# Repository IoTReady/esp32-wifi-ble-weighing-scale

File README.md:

# ESP32 Weighing Scale

This is a weighing scale designed to share data over Wi-Fi using esp32 WROOM32 module.
For the weighing scale we are using a load cell and measuring the output using a HX711 24-bit ADC designed for weigh scales and industrial control applications to interface directly with a bridge sensor.

The final design and gerber files are available [here](https://github.com/IoTReady/esp32-wifi-ble-weighing-scale/blob/master/design/Single_scale_v3_kicad/single_scale_v3_gerber.zip).

# Circuit Design
## Power Supply
We are using a 3.7V Li-Ion battery for powering this scale. The current rating can be changed depending on the use case. We also have a battery charging circuit on the board, so you don't have to remove the battery for charging it.

We use a TP4056 charging IC, as it is easily available and gives a reasonable 1000 mA output current, with 4.2V output voltage for charging the battery. For preventing the battery from over-charging and over-discharging, we use the DW01A protection IC. It is connected with a FS8205A switch IC, which will cut off the battery from the circuit if any fault is detected.

Finally, the 3.7V battery ouput is fed to two voltage regulators to get +5V and +3.3V output voltages as shown below:

## ADC Circuit
We are using HX711 24-bit ADC IC for converting the analog data from the Load cell. We selected HX711 as it is designed specifically for weighing scales, to interface with brige sensors directly. Load cells are basically bridge sensors.
As shown below the final output is in serial data output form. This is basically a UART output, and there are few digital pin controls.

## ESP32
The brains of our weighing scale, the esp32 wroom32 module is a BLE plus WiFi SoC which collects weight data from the ADC circuit and outputs the final processed data via a digital display and WiFi to the selected servers for maintaing inventories or doing any data analysis.

# PCB
This is what the final PCB looks like:

# Firmware

## Features
- 24 bit HX711 as ADC
- Any 4 wire load cell
- BLE communication
- Tare button
- Battery level monitor
- MAX7219 driven 7-segment display
- OTA (to be hosted from local network)
- Console setting of tare value and sensor calibration

### Weight Calculation
The HX711 is a great match for weighing use-cases. The 24 bit ADC is designed specifically for weight measurements and is directly interfaceable with load sensors and weigh bridges. There is no programming needed for the internal registers. All controls to the HX711 are through the pins. The HX711 component handles everything necessary for conversion to calibration. For more details, find the HX711 datasheet [here](https://cdn.sparkfun.com/datasheets/Sensors/ForceFlex/hx711_english.pdf)

### Factors for weight calculation/conversion
There are two major factors to consider in order to get an accurate calculation:
1. Tare Value (OFFSET): In weighment applications it is important to be able to reset the output value to zero if and when needed. In the firmware however, it is particularly important to understand the ADC output at zero. Any value higher or lower than this ADC value would result in positive or negative weight hereafter. Almost all weighing scales will provide a button for the users to return the current weight to zero. This is used to round off any extra weight that needs not be accounted, for example the container. In this application, the tare button has been assigned to GPIO19 on the ESP32.
  The auto-tare feature in the application tares the system at startup, such that the weighing scale always starts with a zero value. This eliminates human error. Make sure that there are no items placed on the platform and even the bottom of the scale is not in contact with any object at the time of starting up the machine until the display shows 0.
  
3. Calibration value (SCALE): The calibration value is the multiplication factor that needs to be multiplied to the ADC output value in order to get the real-time weight out of it in the units needed. This calibration value will be different for all individual load cells, hence it is important that all weighing machines go through a calibration procedure before they are shipped.

This application provides a simple method to set/calculate the above mentioned Tare and Calibration values:
- Start by placing the scale in a stable platform and environment. Please choose an area with minimum air currents and vibration levels.
- Connect your computer to the ESP32 controller's UART0 using an FTDI connector.
- You will need software to access the serial communication happening over the UART lines. For example, [PuTTY](https://www.putty.org/).
- While the program is flashed and running on the ESP32, press 'm' and hit Enter. You will be provided a menu using which you can access the tare and calibration features.
- For calibration, carry out the following steps:
  - You need to select a test value weight. This weight must be within the scale constraint and approximately 50% of the upper capacity. This should also be a known weight that you should possess.
  - Make sure that there are no items placed on the platform and even the bottom of the scale is not in contact with any object.
  - Make sure the console shows 0 weight. If not, press the tare button so the console shows 0.
  - Place the known selected weight on the platform of the weighing scale and view the weight on the console.
  - Follow the instructions to either change the calibration value or select the current selected calibration value if the weight shown on console is correct.
  - Repeat until the weight is correct.
  - Save

### BLE Characteristics:
| Service / Characteristics Name | UUID Handle                          | Properties | Description   |
|--------------------------------|--------------------------------------|------------|---------------|
| Device State Service           | 000000ff-0000-1000-8000-00805f9b34fb | Service    | -             |
| Weight Data                    | 0000ff00-0000-1000-8000-00805f9b34fb | Read       | Weight in kgs |

| Service / Characteristics Name  | UUID Handle                          | Properties  | Description                                                                                                       | Size            | Data Type        |
|---------------------------------|--------------------------------------|-------------|-------------------------------------------------------------------------------------------------------------------|-----------------|------------------|
| System Settings Service         | 000000ee-0000-1000-8000-00805f9b34fb | Service     | -                                                                                                                 | -               | -                |
| Device ID Characteristic        | 0000ee00-0000-1000-8000-00805f9b34fb | Read        | Read Device ID                                                                                                    | Length: 12      | String           |
| WiFi SSID  Characteristic       | 0000ee01-0000-1000-8000-00805f9b34fb | Read/Write  | WiFi SSID configured with the device                                                                              | Max Length: 32  | String           |
| WiFi Password Characteristic    | 0000ee02-0000-1000-8000-00805f9b34fb | Read/Write  | WiFi Password configured with the device                                                                          | Max Length: 32  | String           |
| OTA IP Characteristic           | 0000ee03-0000-1000-8000-00805f9b34fb | Read/Write  | Read/Write the IP of OTA host                                                                                     | Max Length: 100 | String           |
| OTA Port Characteristic         | 0000ee04-0000-1000-8000-00805f9b34fb | Read/Write  | Read/Write the Port of OTA host server                                                                            | Max Length: 100 | String           |
| OTA Filename Characteristic     | 0000ee05-0000-1000-8000-00805f9b34fb | Read/Write  | Read/Write the filename of OTA binary file                                                                        | Max Length: 100 | String           |
| Force OTA Characteristic        | 0000ee06-0000-1000-8000-00805f9b34fb | Write       | Initiate OTA procedure Value: ‘1’ [0x31]                                                                          | 1 byte          | Unsigned Integer |
| Tare Weight Characteristic      | 0000ee07-0000-1000-8000-00805f9b34fb | Write       | Cancel OTA procedure within 10 seconds of initiation Value: ‘1’ [0x31]                                            | 1 byte          | Unsigned Integer |
| Connect WiFi Characteristic     | 0000ee08-0000-1000-8000-00805f9b34fb | Write       | Connect to previously configured WiFi credentials. Value: ‘1’ [0x31]                                              | 1 byte          | Unsigned Integer |
| Software Version Characteristic | 0000ee09-0000-1000-8000-00805f9b34fb | Read        | Read the Software Version in the device                                                                           | -               | String           |
# Applications
This weighing scale is designed keeping in mind sharing of data over the internet. So, any application where we need to capture weight of things and maintain a record for any use, we can integrate this device in that system.

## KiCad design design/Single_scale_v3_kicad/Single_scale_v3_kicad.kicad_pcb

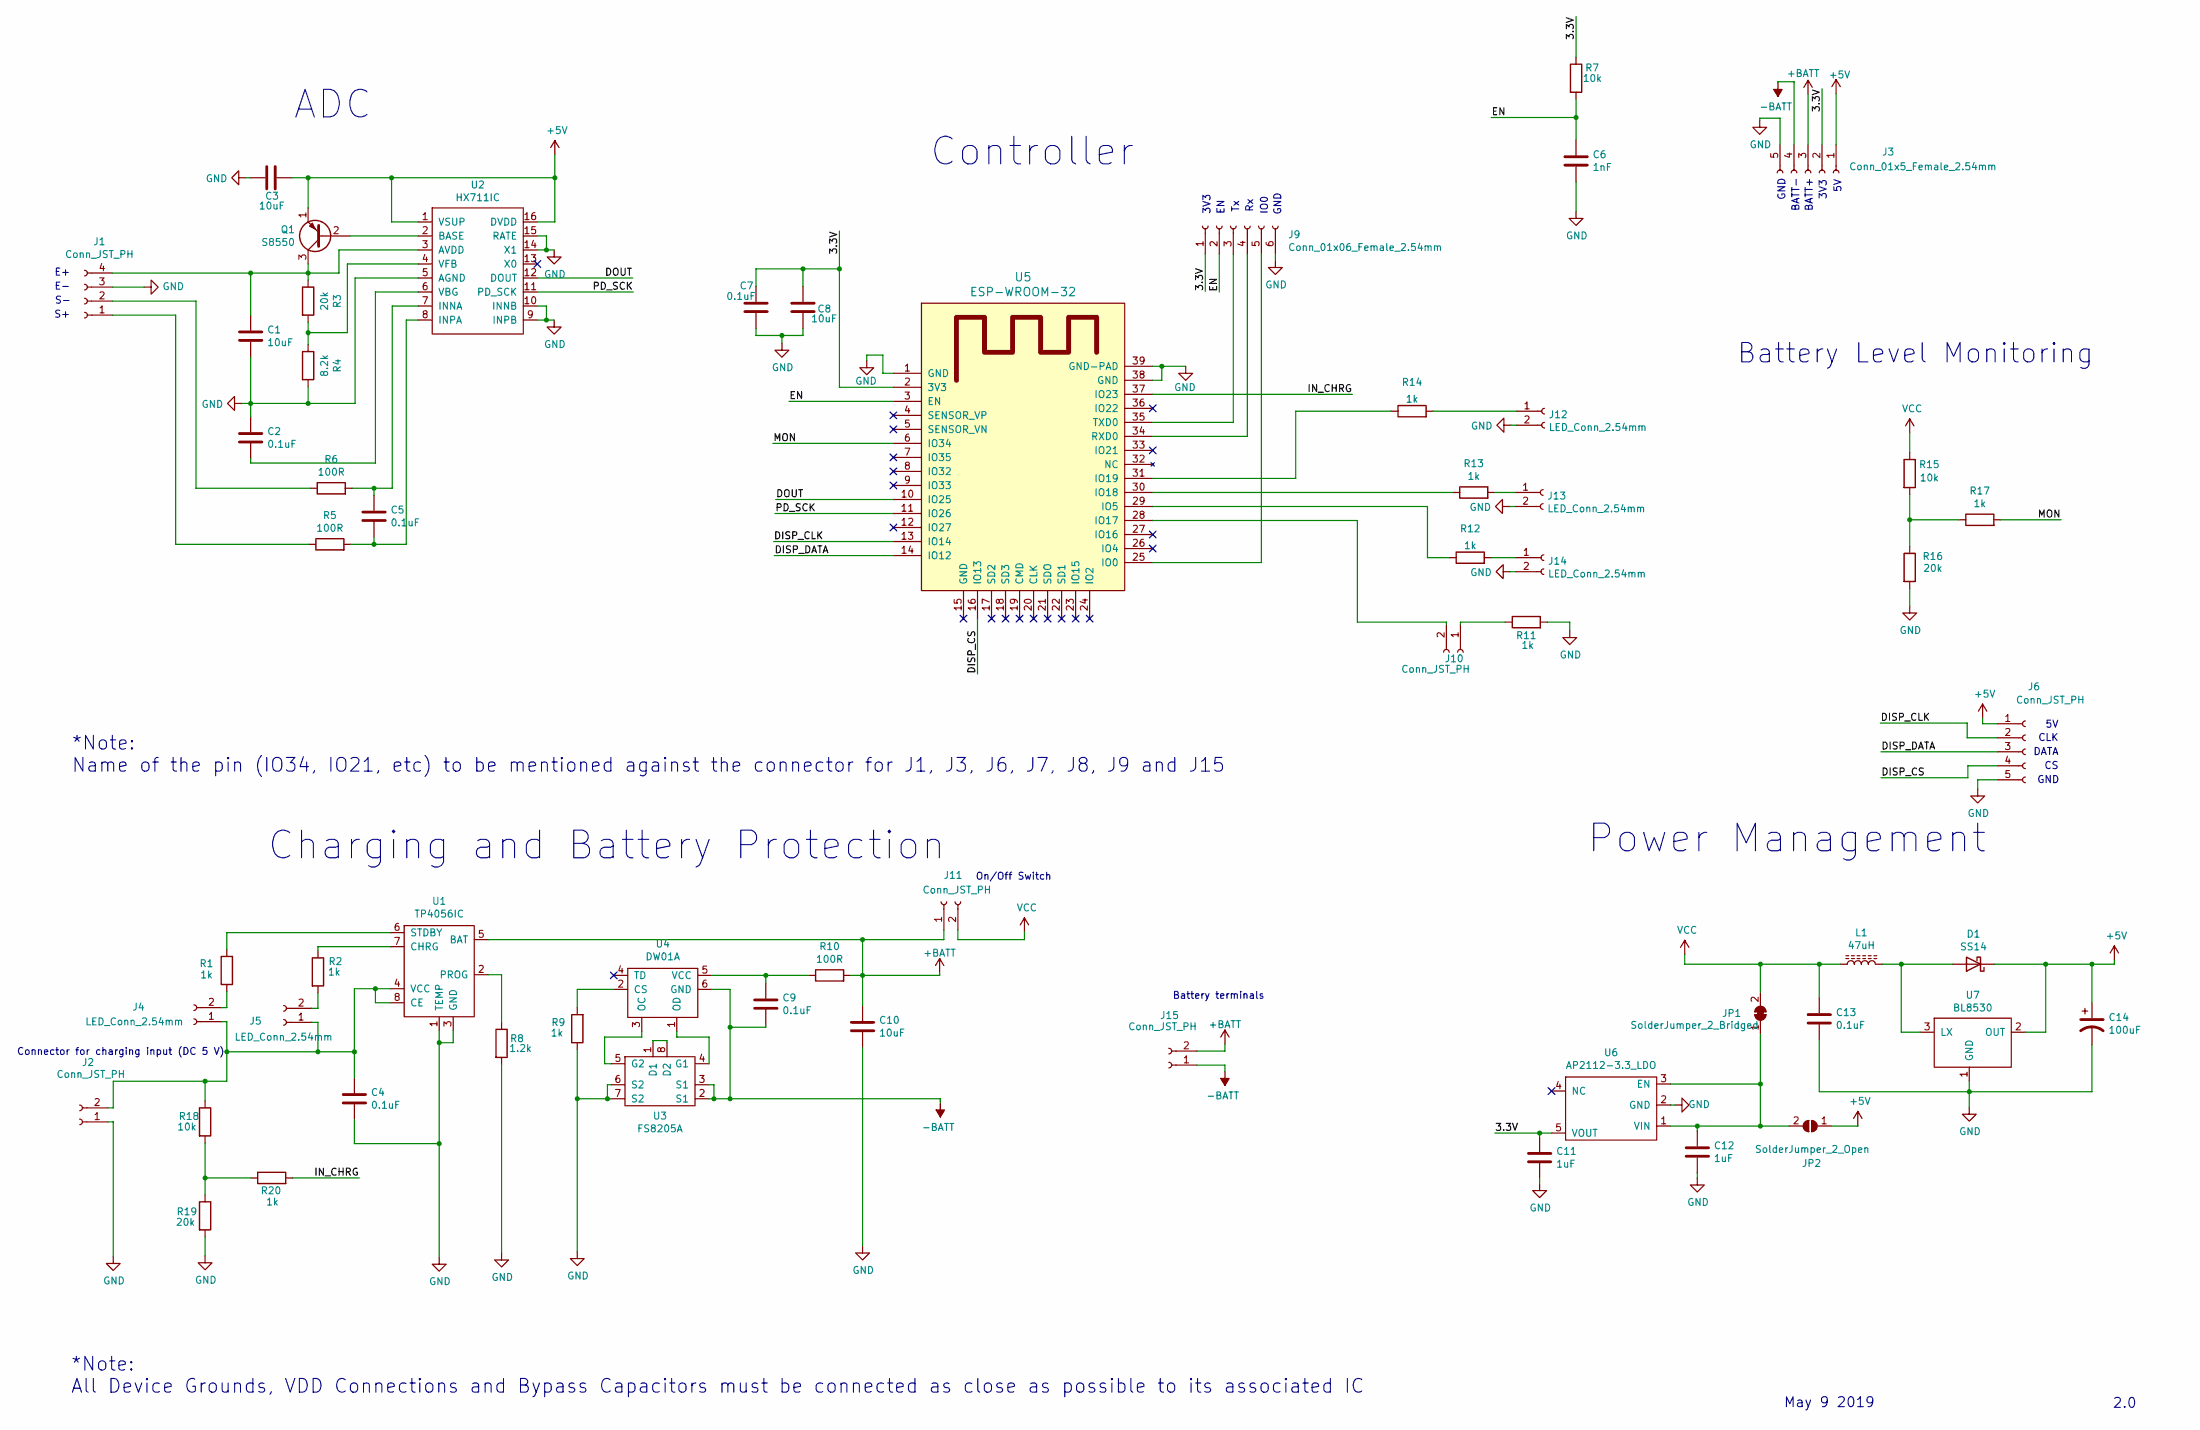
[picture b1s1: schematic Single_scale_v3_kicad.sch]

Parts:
C1, C3, C8, C10: 10uF; C_0603_1608Metric
C2, C4, C5, C7, C9, C13: 0.1uF; C_0603_1608Metric
C6: 1nF; C_0603_1608Metric
C11, C12: 1uF; C_0603_1608Metric
C14: 100uF; CP_Elec_6.3x5.4
D1: SS14; D_SMA
J1: Conn_JST_PH; JST_PH_B4B-PH-K_1x04_P2.00mm_Vertical
J2, J10, J11, J15: Conn_JST_PH; JST_EH_B2B-EH-A_1x02_P2.50mm_Vertical
J3: Conn_01x5_Female_2.54mm; PinHeader_1x05_P2.54mm_Vertical
J4, J5, J12, J13, J14: LED_Conn_2.54mm; PinHeader_1x02_P2.54mm_Vertical
J6: Conn_JST_PH; JST_PH_B5B-PH-K_1x05_P2.00mm_Vertical
J9: Conn_01x06_Female_2.54mm; PinHeader_1x06_P2.54mm_Vertical
JP1: SolderJumper_2_Bridged; SolderJumper-2_P1.3mm_Bridged2Bar_Pad1.0x1.5mm
JP2: SolderJumper_2_Open; SolderJumper-2_P1.3mm_Open_Pad1.0x1.5mm
L1: 47uH; L_Taiyo-Yuden_MD-5050
Q1: S8550; SOT-23_modified
R1, R2, R9, R11, R12, R13, R14, R17, R20: 1k; R_0603_1608Metric
R3, R16, R19: 20k; R_0603_1608Metric
R4: 8.2k; R_0603_1608Metric
R5, R6, R10: 100R; R_0603_1608Metric
R7, R15, R18: 10k; R_0603_1608Metric
R8: 1.2k; R_0603_1608Metric
U1: TP4056IC; SOP-8
U2: HX711IC; SOP-16_4.55x10.3mm_P1.27mm
U3: FS8205A; TSSOP-8_4.4x3mm_P0.65mm
U4: DW01A; SOT-23-6
U5: ESP-WROOM-32; MODULE_ESP32-WROOM-32
U6: AP2112-3.3_LDO; SOT-23-5
U7: BL8530; SOT-89-3

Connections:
+5V: C3.1, C14.1, D1.1 (K), J3.1, J6.1, JP2.1 (A), Q1.1 (E), U2.1 (VSUP), U2.16 (DVDD), U7.2 (OUT)
+BATT: C10.1, J3.3, J11.1, J15.2, R10.2, U1.5 (BAT)
-BATT: C9.2, J3.4, J15.1, U3.2 (S1), U3.3 (S1), U4.6 (GND)
/3.3V: C7.1, C8.1, C11.1, J3.2, J9.1, R7.1, U5.2 (3V3), U6.5 (VOUT)
/DISP_CLK: J6.2, U5.13 (IO14)
/DISP_CS: J6.4, U5.16 (IO13)
/DISP_DATA: J6.3, U5.14 (IO12)
/DOUT: U2.12 (DOUT), U5.10 (IO25)
/EN: C6.1, J9.2, R7.2, U5.3 (EN)
/IN_CHRG: R20.2, U5.37 (IO23)
/MON: R17.2, U5.6 (IO34)
/PD_SCK: U2.11 (PD_SCK), U5.11 (IO26)
GND: C1.2, C2.1, C3.2, C4.2, C6.2, C7.2, C8.2, C10.2, C11.2, C12.2, C13.2, C14.2, J1.3, J2.1, J3.5, J6.5, J9.6, J12.2, J13.2, J14.2, R4.2, R8.2, R9.1, R11.2, R16.2, R19.2, U1.1 (TEMP), U1.3 (GND), U2.5 (AGND), U2.9 (INPB), U2.10 (INNB), U2.14 (X1), U2.15 (RATE), U3.6 (S2), U3.7 (S2), U5.1 (GND), U5.38 (GND), U5.39 (GND-PAD), U6.2 (GND), U7.1 (GND)
unnamed: C1.1, J1.4, Q1.3 (C), R3.1, U2.3 (AVDD)
unnamed: C2.2, U2.6 (VBG)
unnamed: C4.1, J2.2, J4.1, J5.1, R18.1, U1.4 (VCC), U1.8 (CE)
unnamed: C5.1, R6.2, U2.7 (INNA)
unnamed: C5.2, R5.2, U2.8 (INPA)
unnamed: C9.1, R10.1, U4.5 (VCC)
unnamed: C12.1, JP1.1 (A), JP2.2 (B), U6.1 (VIN), U6.3 (EN)
unnamed: D1.2 (A), L1.2, U7.3 (LX)
unnamed: J1.1, R5.1
unnamed: J1.2, R6.1
unnamed: J4.2, R1.1
unnamed: J5.2, R2.2
unnamed: J9.3, U5.35 (TXD0)
unnamed: J9.4, U5.34 (RXD0)
unnamed: J9.5, U5.25 (IO0)
unnamed: J10.1, R11.1
unnamed: J10.2, U5.28 (IO17)
unnamed: J12.1, R14.2
unnamed: J13.1, R13.2
unnamed: J14.1, R12.2
unnamed: Q1.2 (B), U2.2 (BASE)
unnamed: R1.2, U1.6 (STDBY)
unnamed: R2.1, U1.7 (CHRG)
unnamed: R3.2, R4.1, U2.4 (VFB)
unnamed: R8.1, U1.2 (PROG)
unnamed: R9.2, U4.2 (CS)
unnamed: R12.1, U5.29 (IO5)
unnamed: R13.1, U5.30 (IO18)
unnamed: R14.1, U5.31 (IO19)
unnamed: R15.2, R16.1, R17.1
unnamed: R18.2, R19.1, R20.1
unnamed: U3.1 (D1), U3.8 (D2)
unnamed: U3.4 (G1), U4.1 (OD)
unnamed: U3.5 (G2), U4.3 (OC)
VCC: C13.1, J11.2, JP1.2 (B), L1.1, R15.1

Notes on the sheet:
Charging and Battery Protection
Power Management
ADC
Battery Level Monitoring
Controller
May 9 2019
2.0
*Note: All Device Grounds, VDD Connections and Bypass Capacitors must be connected as close as possible to its associated IC
*Note: Name of the pin (IO34, IO21, etc) to be mentioned against the connector for J1, J3, J6, J7, J8, J9 and J15
GND
BATT-
BATT+
3V3
IO0
DATA
CLK
Connector for charging input (DC 5 V)
Battery terminals
On/Off Switch

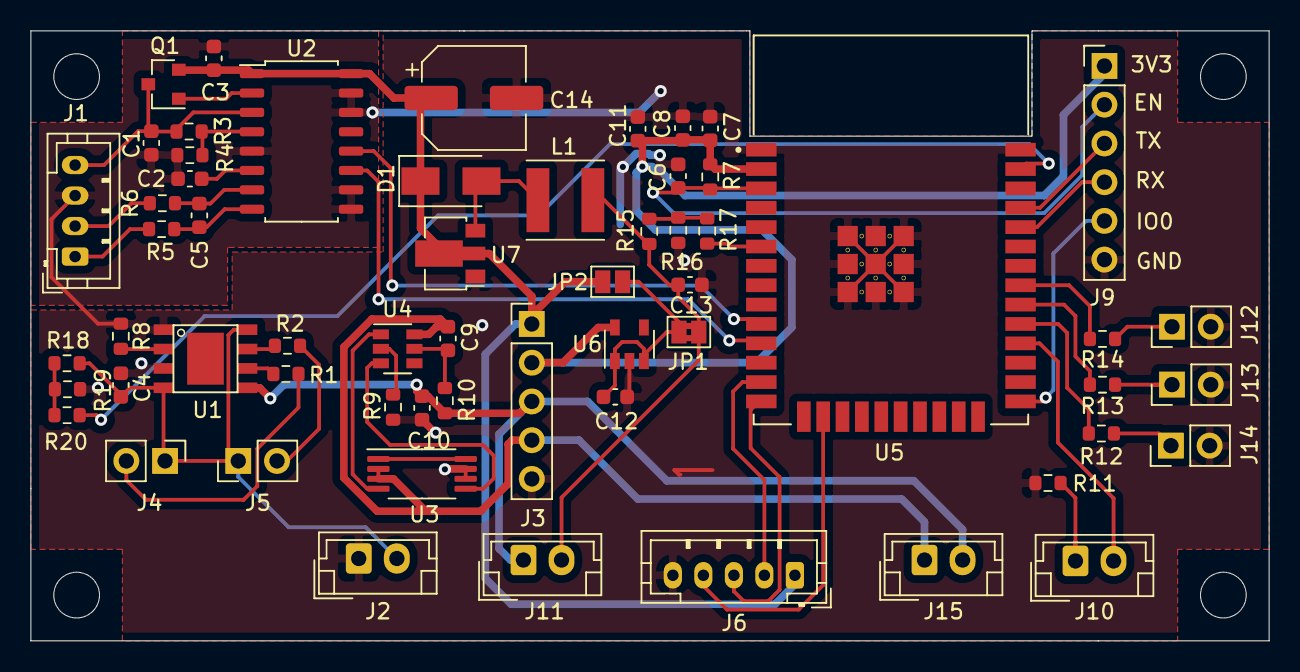
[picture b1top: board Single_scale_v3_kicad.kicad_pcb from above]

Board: 2 copper layers, 81.2 x 40.0 mm, 59 parts (0 on the bottom side), 48 nets.

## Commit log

2021-06-06 added firmware to README
2021-06-06 added BLE chars to READMe
2021-06-06 Reviewed
2021-06-12 Adds license info
2021-06-18 Fix broken links in README
